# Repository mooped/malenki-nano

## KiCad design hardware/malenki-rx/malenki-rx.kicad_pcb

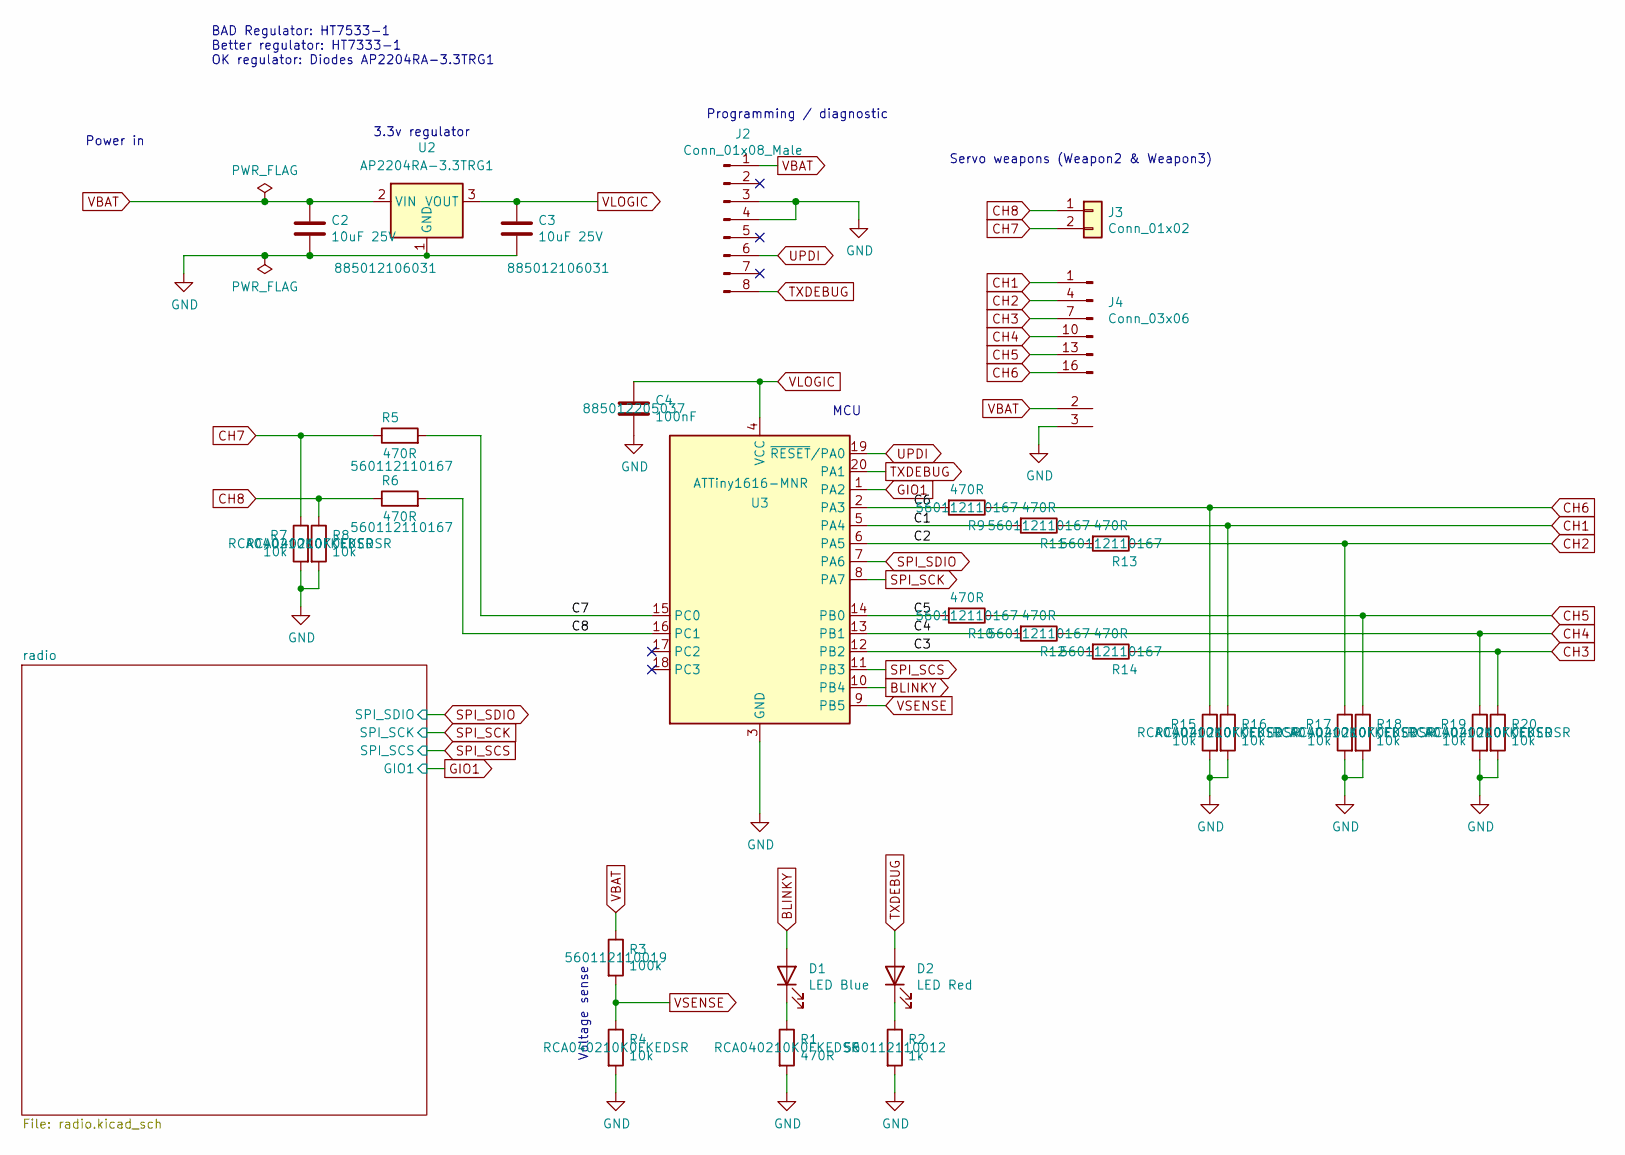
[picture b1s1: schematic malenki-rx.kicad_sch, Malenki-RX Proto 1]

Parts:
C2, C3: 10uF 25V; C_0603_1608Metric; MPN 885012106031; LCSC C96446
C4: 100nF; C_0402_1005Metric_Pad0.74x0.62mm_HandSolder; Partnum C14663; LCSC C307331
D1: LED Blue; LED_0603_1608Metric; MPN 19-217/BHC-ZL1M2RY/3T; LCSC C72041
D2: LED Red; LED_0603_1608Metric; MPN KT-0603R; LCSC C2286
J2: Conn_01x08_Male; SOIC_clipProgSmall
J3: Conn_01x02; wirepad_2
J4: Conn_03x06; ServoHeader_3x06_P2.54mm_Vertical
R1: 470R; R_0402_1005Metric; MPN RCA040210K0FKEDSR; LCSC C25117
R2: 1k; R_0402_1005Metric; MPN 560112110012; LCSC C11702
R3: 100k; R_0402_1005Metric; MPN 560112110019; LCSC C25741
R4, R7, R8, R15, R16, R17, R18, R19, R20: 10k; R_0402_1005Metric; Partnum C25804; LCSC C25744
R5, R6, R9, R10, R11, R12, R13, R14: 470R; R_0402_1005Metric; MPN 560112110167; LCSC C25117
U2: AP2204RA-3.3TRG1; SOT-89-3; LCSC C151625
U3: ATTiny1616-MNR; VQFN-20-1EP_3x3mm_P0.4mm_EP1.7x1.7mm; MPN ATtiny1616-MNR; LCSC C507118

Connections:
/C1: R11.2, U3.5 (PA4)
/C2: R13.2, U3.6 (PA5)
/C3: R14.2, U3.12 (PB2)
/C4: R12.2, U3.13 (PB1)
/C5: R10.2, U3.14 (PB0)
/C6: R9.2, U3.2 (PA3)
/C7: R5.2, U3.15 (PC0)
/C8: R6.2, U3.16 (PC1)
BLINKY: D1.2 (A), U3.10 (PB4)
CH1: J4.1 (Sig_1), R11.1, R16.1
CH2: J4.4 (Sig_2), R13.1, R17.1
CH3: J4.7 (Sig_3), R14.1, R20.1
CH4: J4.10 (Sig_4), R12.1, R19.1
CH5: J4.13 (Sig_5), R10.1, R18.1
CH6: J4.16 (Sig_6), R9.1, R15.1
CH7: J3.2, R5.1, R7.1
CH8: J3.1, R6.1, R8.1
GIO1: U3.1 (PA2); also elsewhere on the board
GND: C2.2, C3.2, C4.2, J2.3, J2.4, J4.3 (GND_1), J4.6 (GND_2), J4.9 (GND_3), J4.12 (GND_4), J4.15 (GND_5), J4.18 (GND_6), R1.2, R2.2, R4.2, R7.2, R8.2, R15.2, R16.2, R17.2, R18.2, R19.2, R20.2, U2.1 (GND), U3.3 (GND), U3.21 (GND); also elsewhere on the board
unnamed: D1.1 (K), R1.1
unnamed: D2.1 (K), R2.1
SPI_SCK: U3.8 (PA7); also elsewhere on the board
SPI_SCS: U3.11 (PB3); also elsewhere on the board
SPI_SDIO: U3.7 (PA6); also elsewhere on the board
TXDEBUG: D2.2 (A), J2.8, U3.20 (PA1)
UPDI: J2.6, U3.19 (~RESET/PA0)
VBAT: C2.1, J2.1, J4.2 (V_1), J4.5 (V_2), J4.8 (V_3), J4.11 (V_4), J4.14 (V_5), J4.17 (V_6), R3.1, U2.2 (VIN)
VLOGIC: C3.1, C4.1, U2.3 (VOUT), U3.4 (VCC); also elsewhere on the board
VSENSE: R3.2, R4.1, U3.9 (PB5)

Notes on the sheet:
Voltage sense
Power in
Servo weapons (Weapon2 & Weapon3)
Programming / diagnostic
BAD Regulator: HT7533-1 Better regulator: HT7333-1 OK regulator: Diodes AP2204RA-3.3TRG1
MCU
3.3v regulator

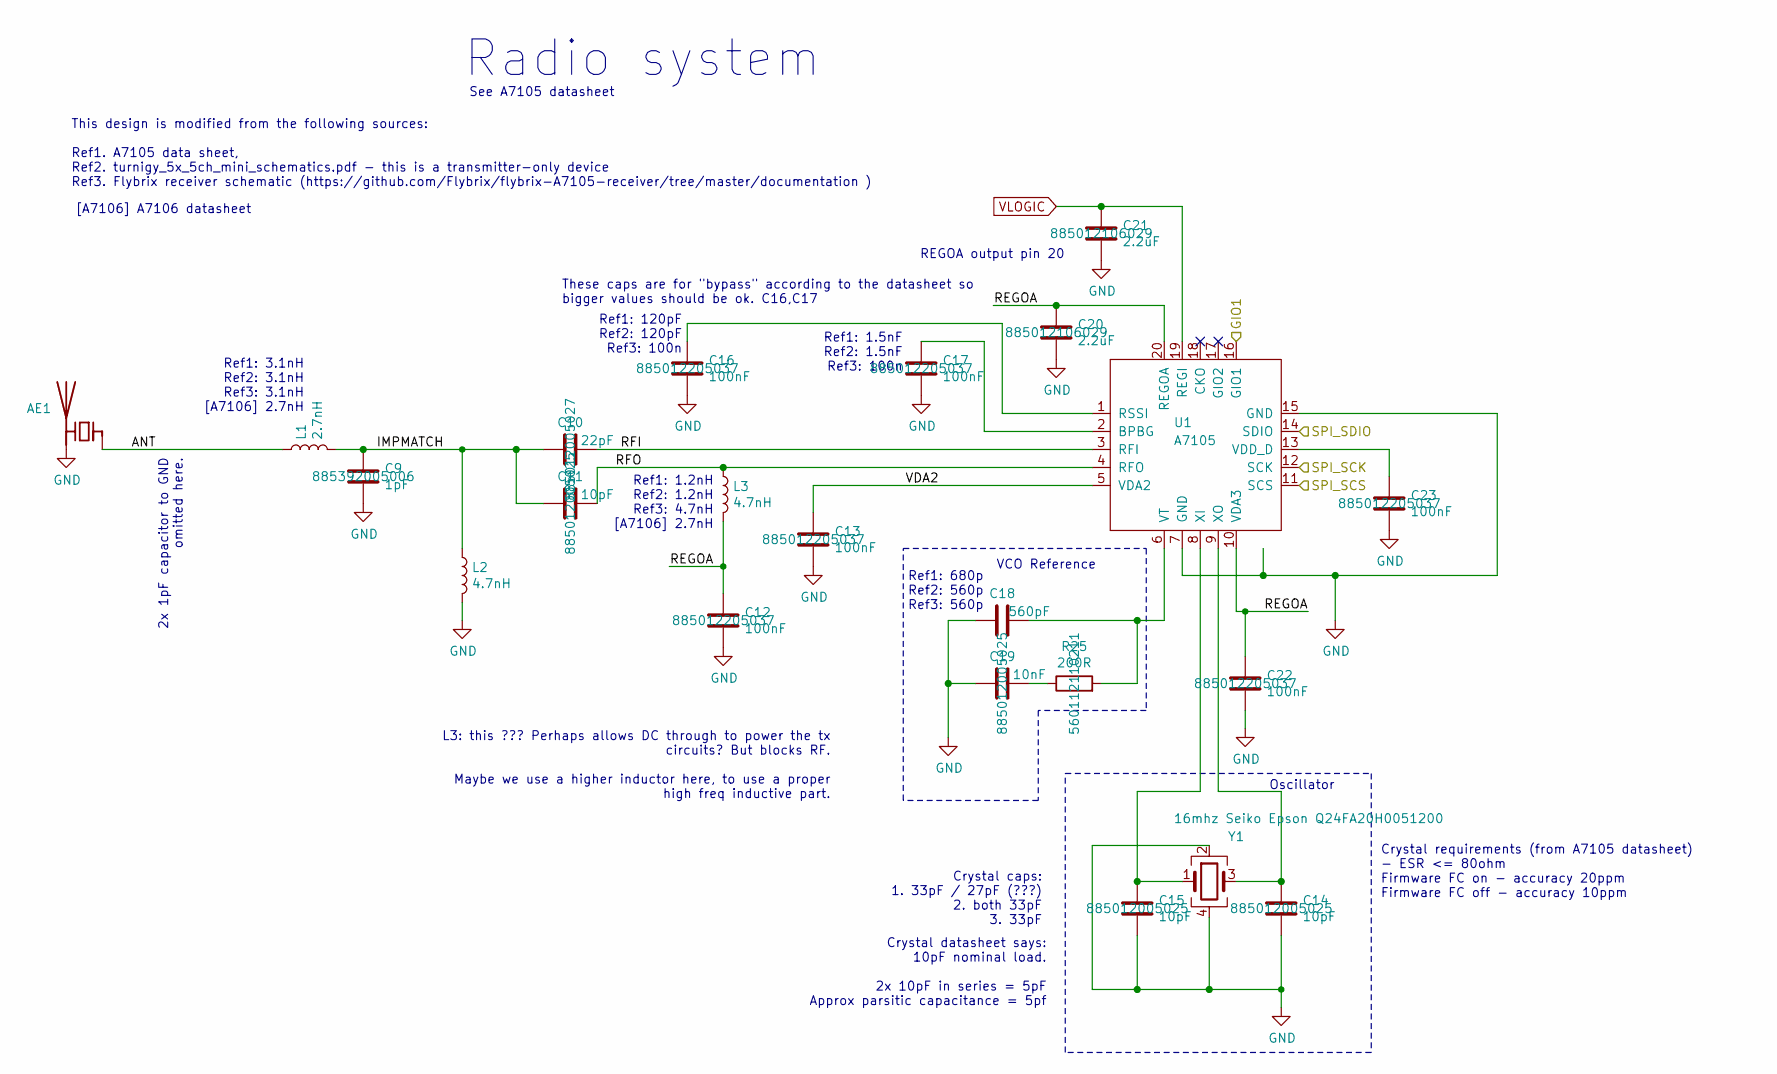
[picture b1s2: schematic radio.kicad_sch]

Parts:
AE1: malenki_antenna
C9: 1pF; C_0402_1005Metric_Pad0.74x0.62mm_HandSolder; MPN 885392005006; LCSC C1550
C10: 22pF; C_0402_1005Metric_Pad0.74x0.62mm_HandSolder; MPN 885012005027; LCSC C1555
C11, C14, C15: 10pF; C_0402_1005Metric_Pad0.74x0.62mm_HandSolder; MPN 885012005025; LCSC C32949
C12, C13, C16, C17, C22, C23: 100nF; C_0402_1005Metric_Pad0.74x0.62mm_HandSolder; MPN 885012205037; LCSC C307331
C18: 560pF; C_0402_1005Metric_Pad0.74x0.62mm_HandSolder; MPN CL05C561JB5NNNC; LCSC C1539
C19: 10nF; C_0402_1005Metric_Pad0.74x0.62mm_HandSolder; MPN 885012005025; LCSC C15195
C20, C21: 2.2uF; C_0603_1608Metric; MPN 885012106029; LCSC C23630
L1: 2.7nH; L_0402_1005Metric_Pad0.77x0.64mm_HandSolder; LCSC C76791
L2: 4.7nH; L_0402_1005Metric_Pad0.77x0.64mm_HandSolder; MPN LQW15AN4N7D10D; LCSC C341688
L3: 4.7nH; L_0402_1005Metric_Pad0.77x0.64mm_HandSolder; MPN VHF160808H4N7ST; LCSC C341688
R25: 200R; R_0402_1005Metric; MPN 560112110211; LCSC C25087
U1: A7105; a7105-QFN-20; MPN A71X05AQFI/Q; LCSC C126376
Y1: 16mhz Seiko Epson Q24FA20H0051200; Crystal_SMD_2520-4Pin_2.5x2.0mm; MPN Q24FA20H0051200; LCSC C255947

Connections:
/radio/ANT: AE1.1 (FEED), L1.1
/radio/IMPMATCH: C9.1, C10.1, C11.1, L1.2, L2.1
/radio/REGOA: C12.1, C20.1, C22.1, L3.2, U1.10 (VDA3), U1.20 (REGOA)
/radio/RFI: C10.2, U1.3 (RFI)
/radio/RFO: C11.2, L3.1, U1.4 (RFO)
/radio/VDA2: C13.1, U1.5 (VDA2)
GIO1: U1.16 (GIO1); also elsewhere on the board
GND: AE1.2 (PCB_Trace), C9.2, C12.2, C13.2, C14.2, C15.2, C16.2, C17.2, C18.1, C19.2, C20.2, C21.2, C22.2, C23.2, L2.2, U1.7 (GND), U1.15 (GND), U1.21 (GND), Y1.2, Y1.4; also elsewhere on the board
unnamed: C19.1, R25.1
unnamed: C17.1, U1.2 (BPBG)
unnamed: C16.1, U1.1 (RSSI)
unnamed: C23.1, U1.13 (VDD_D)
unnamed: C18.2, R25.2, U1.6 (VT)
unnamed: C15.1, U1.8 (XI), Y1.1
unnamed: C14.1, U1.9 (XO), Y1.3
SPI_SCK: U1.12 (SCK); also elsewhere on the board
SPI_SCS: U1.11 (SCS); also elsewhere on the board
SPI_SDIO: U1.14 (SDIO); also elsewhere on the board
VLOGIC: C21.1, U1.19 (REGI); also elsewhere on the board

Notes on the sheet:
REGOA output pin 20
Radio system
Ref1: 3.1nH Ref2: 3.1nH Ref3: 3.1nH [A7106] 2.7nH
See A7105 datasheet
Ref1: 120pF Ref2: 120pF Ref3: 100n
Crystal datasheet says: 10pF nominal load. 2x 10pF in series = 5pF Approx parsitic capacitance = 5pf
Oscillator
Ref1: 1.2nH Ref2: 1.2nH Ref3: 4.7nH [A7106] 2.7nH
L3: this ??? Perhaps allows DC through to power the tx circuits? But blocks RF. Maybe we use a higher inductor here, to use a proper high freq inductive part.
Crystal requirements (from A7105 datasheet) - ESR <= 80ohm Firmware FC on - accuracy 20ppm Firmware FC off - accuracy 10ppm
[A7106] A7106 datasheet
These caps are for "bypass" according to the datasheet so bigger values should be ok. C16,C17
Ref1: 680p Ref2: 560p Ref3: 560p
VCO Reference
2x 1pF capacitor to GND omitted here.
This design is modified from the following sources: Ref1. A7105 data sheet, Ref2. turnigy_5x_5ch_mini_schematics.pdf - this is a transmitter-only device Ref3. Flybrix receiver schematic (https://github.com/Flybrix/flybrix-A7105-receiver/tree/master/documentation )
Crystal caps: 1. 33pF / 27pF (???) 2. both 33pF 3. 33pF
Ref1: 1.5nF Ref2: 1.5nF Ref3: 100n

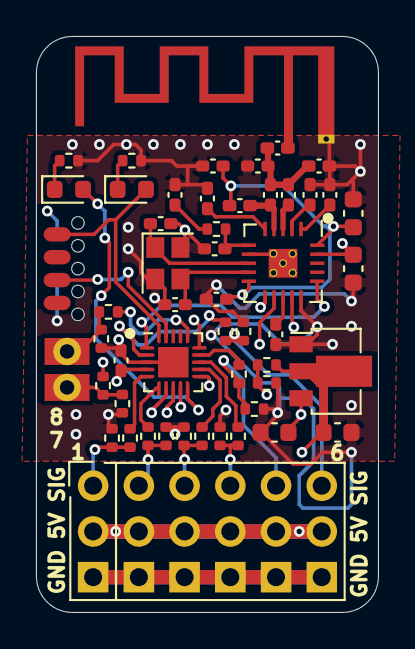
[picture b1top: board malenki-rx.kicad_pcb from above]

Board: 4 copper layers, 19.0 x 32.0 mm, 52 parts (1 on the bottom side), 42 nets.

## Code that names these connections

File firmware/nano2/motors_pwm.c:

#include "motors.h"
#include "diag.h"
#include "state.h"
#include "weapons.h"

#include <avr/io.h>
#include <avr/interrupt.h>
#include <stdlib.h>
#include <stdbool.h>

#define F_CPU 10000000 /* 10MHz */
#include <util/delay.h>

#define NUM_CHANNELS 6  // 6 channels as outputs and one for the downtime

#define OUTPUT_7_STICK 6
#define OUTPUT_8_STICK 7

#define INT_MASK (TCA_SINGLE_CMP0_bm | TCA_SINGLE_OVF_bm)

// Desired PWM values for each output
volatile uint16_t pwm_values[NUM_CHANNELS] = { 0, 0, 0, 0, 0, 0 };
volatile uint16_t pwm_values_buffered[NUM_CHANNELS] = { 0, 0, 0, 0, 0, 0 };

// Track which channel is being output
volatile uint16_t active_channel = 0;

// RX board has slightly wonky pin ordering to simplify layout
//
//   PA3 - Ch 6
//   PA4 - Ch 1
//   PA5 - Ch 2
//
//   PB0 - Ch 5
//   PB1 - Ch 4
//   PB2 - Ch 3

static volatile uint8_t* portclr_map[NUM_CHANNELS] =
{
    &(PORTA.OUTCLR),
    &(PORTA.OUTCLR),
    &(PORTB.OUTCLR),
    &(PORTB.OUTCLR),
    &(PORTB.OUTCLR),
    &(PORTA.OUTCLR),
};

static volatile uint8_t* portset_map[NUM_CHANNELS] =
{
    &(PORTA.OUTSET),
    &(PORTA.OUTSET),
    &(PORTB.OUTSET),
    &(PORTB.OUTSET),
    &(PORTB.OUTSET),
    &(PORTA.OUTSET),
};

static volatile uint8_t portmask_map[NUM_CHANNELS] =
{
    (1 << 4),
    (1 << 5),
    (1 << 2),
    (1 << 1),
    (1 << 0),
    (1 << 3),
};

static bool pin_check(char portname, PORT_t *port, uint8_t pin)
{
    uint8_t bm = 1<<pin;
    // Set the pin as an input
    port->DIRCLR = bm;
    // Wait a very tiny time
    _delay_ms(1);
    bool state = (port->IN & bm);
    if (state) {
        // High!
        diag_println("motor pin_check FAIL: port %c %d stuck high",
            portname, pin);
        return false;
    }
    return true;
}

static void motors_check()
{
    // Check that all of our outputs are working
    // Onboard pull down resistors should hold the signal lines all low.
    // If any are high, it is an error.
    // pwm outputs = PB0,1,2 and PA3,4,5
    bool ok = true;
    ok = ok && pin_check('A', &PORTA,3);
    ok = ok && pin_check('A', &PORTA,4);
    ok = ok && pin_check('A', &PORTA,5);
    ok = ok && pin_check('B', &PORTB,0);
    ok = ok && pin_check('B', &PORTB,1);
    ok = ok && pin_check('B', &PORTB,2);
    if (! ok) {
        diag_println("Motor pin stuck high"); // never returns
        diag_println("Continuing anyway");
    }
}

void motors_init()
{
    motors_check();
    // Set all the ports which need to be outputs, to be outputs.
    // should all be low initially.
    // pwm outputs = PB0,1,2 and PA3,4,5
    // PB0, PB1, PB2
    // clear initial output
    PORTB.OUTCLR = 1 << 0;
    PORTB.OUTCLR = 1 << 1;
    PORTB.OUTCLR = 1 << 2;
    PORTA.OUTCLR = 1 << 3;
    PORTA.OUTCLR = 1 << 4;
    PORTA.OUTCLR = 1 << 5;
    // set directions to out
    PORTB.DIRSET = 1 << 0;
    PORTB.DIRSET = 1 << 1;
    PORTB.DIRSET = 1 << 2;
    PORTA.DIRSET = 1 << 3;
    PORTA.DIRSET = 1 << 4;
    PORTA.DIRSET = 1 << 5;

    // Timer A in 16 bit mode
    // Setting pins in motors_loop and clearing in CMP0 interrupt
    uint16_t period_val = 16300;
    uint16_t cmp_val = 10000;
    TCA0.SINGLE.CTRLB = TCA_SINGLE_WGMODE_SINGLESLOPE_gc;
    TCA0.SINGLE.INTCTRL = INT_MASK;
    TCA0.SINGLE.PERL = period_val & 0xff;
    TCA0.SINGLE.PERH = (period_val & 0xff00) >> 8;
    TCA0.SINGLE.CMP0L = (cmp_val & 0xff);
    TCA0.SINGLE.CMP0H = (cmp_val & 0xff00) >> 8;
    TCA0.SINGLE.INTFLAGS = 0;
    TCA0.SINGLE.CTRLA = TCA_SINGLE_CLKSEL_DIV2_gc | TCA_SINGLE_ENABLE_bm;

    // Set TCA0 CMP0 vector as the high priority interrupt
    CPUINT.LVL1VEC = TCA0_CMP0_vect_num;
}
void set_motor_direction_duty(uint8_t motor_id, int16_t direction_and_duty)
{
    // Not a thing on this board
}

void enable_motor_brake(uint8_t motor_id)
{
    // Not a thing on this board
}

void motors_loop()
{
  // Update channel data
  for (int channel_index = 0; channel_index < NUM_CHANNELS; ++channel_index)
  {
    pwm_values[channel_index] = pwm_values_buffered[channel_index];
  }
}

void motors_all_off()
{
  // Set all outputs to failsafe values - just flatline
  for (int channel_index = 0; channel_index < NUM_CHANNELS; ++channel_index)
  {
    pwm_values_buffered[channel_index] = 0;
  }
}

void set_pwm_outputs(uint16_t* sticks)
{
  // Buffer the new values for each channel
  uint16_t sum = 0;
  for (int channel_index = 0; channel_index < NUM_CHANNELS; ++channel_index)
  {
    sum += sticks[channel_index];
    pwm_values_buffered[channel_index] = sticks[channel_index];
  }

  // Update weapon channels
  weapons_set(sticks[OUTPUT_7_STICK], sticks[OUTPUT_8_STICK]);
}

ISR(TCA0_CMP0_vect)
{
  // Clear the current channel
  *portclr_map[active_channel] = portmask_map[active_channel];

  active_channel = (active_channel + 1) % NUM_CHANNELS;

  // Update the timer for the next pulse
  uint16_t cmp_val = pwm_values[active_channel] * 5;
  TCA0.SINGLE.CMP0BUFL = (cmp_val & 0xff);
  TCA0.SINGLE.CMP0BUFH = (cmp_val & 0xff00) >> 8;

  // Clear interrupt flag
  TCA0.SINGLE.INTFLAGS = TCA_SINGLE_CMP0_bm;
}

ISR(TCA0_OVF_vect)
{
  // Set the next pin, unless we're oututting no pulse for failsafe
  if (pwm_values[active_channel] != 0)
  {
    *portset_map[active_channel] = portmask_map[active_channel];
  }

  // Reset counter and adjust slightly
  TCA0.SINGLE.CNTL = 50;
  TCA0.SINGLE.CNTH = 0;

  // Clear interrupt flag
  TCA0.SINGLE.INTFLAGS = TCA_SINGLE_OVF_bm;
}

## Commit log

2026-01-04 Malenki-rx with 8 PWM outputs. Prototype 1 as ordered from Aisler.
2026-01-04 Cleanup old BOM Add a very important crab logo
2026-01-04 Fix the crab
2026-01-22 Add interactive HTML BOM
2026-01-25 Add rx board with attiny1616 Makefile Add avr libc paths to common.mk
2026-01-26 WIP: TCA0 split PWM with solid highs and lows
2026-02-01 6 channel of PWM using TCA0 in 16 bit mode via CMP0 interrupt TODO: implement downtime for 20ms period TODO: investigate radio timings and try to sync pulse outputs to end when we're not expecting in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
2026-02-02 Rework interrupt driven PWM output slightly (still not satisfactory)
2026-02-03 Tweak timings for as close as possible to 50hz cycles Set TCA0 CMP interrupt as LVL1 priority to avoid timing jitter Reset counter in TCA0 OVF interrupt to remove jitter at the start of the pulse and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
2026-02-05 Implement channels 7 and 8 on the aux pins
